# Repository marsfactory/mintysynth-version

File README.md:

# mintysynth-version
Rediseño de pcb del proyecto original de Andrew Mowry disponible en https://mintysynth.com/

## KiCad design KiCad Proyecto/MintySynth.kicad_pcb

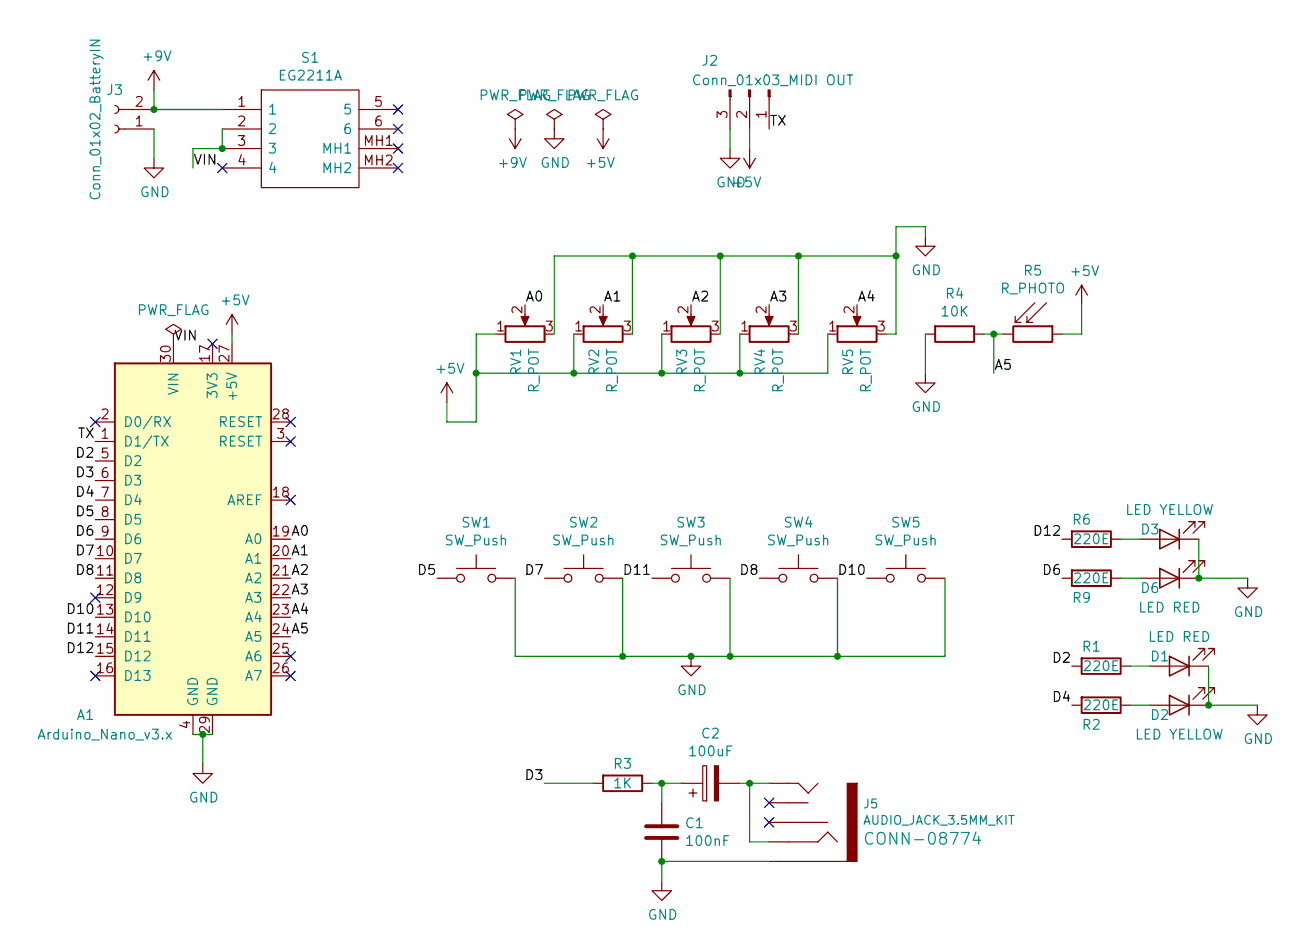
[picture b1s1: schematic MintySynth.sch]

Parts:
A1: Arduino_Nano_v3.x; Arduino_Nano
C1: 100nF; C_Disc_D3.8mm_W2.6mm_P2.50mm
C2: 100uF; CP_Radial_D5.0mm_P2.50mm
D1, D6: LED RED; LED_D5.0mm
D2, D3: LED YELLOW; LED_D5.0mm
J2: Conn_01x03_MIDI OUT; 1X03_LOCK
J3: Conn_01x02_BatteryIN; 1X02
J5: AUDIO_JACK_3.5MM_KIT; AUDIO-JACK-KIT
R1, R2, R6, R9: 220E; R_Axial_DIN0207_L6.3mm_D2.5mm_P10.16mm_Horizontal
R3: 1K; R_Axial_DIN0207_L6.3mm_D2.5mm_P10.16mm_Horizontal
R4: 10K; R_Axial_DIN0207_L6.3mm_D2.5mm_P10.16mm_Horizontal
R5: R_PHOTO; Resistor_LDR_5x4.1_RM3
RV1, RV2, RV3, RV4, RV5: R_POT; Potentiometer_Omeg_PC16PU_Horizontal_MountLS
S1: EG2211A; Mouser Part Number 612-EG2211A
SW1, SW2, SW3, SW4, SW5: SW_Push; SW_PUSH_6mm

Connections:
+5V: A1.27 (+5V), J2.2, R5.1, RV1.1, RV2.1, RV3.1, RV4.1, RV5.1
+9V: J3.2, S1.1
/A0: A1.19 (A0), RV1.2
/A1: A1.20 (A1), RV2.2
/A2: A1.21 (A2), RV3.2
/A3: A1.22 (A3), RV4.2
/A4: A1.23 (A4), RV5.2
/A5: A1.24 (A5), R4.1, R5.2
/D2: A1.5 (D2), R1.2
/D3: A1.6 (D3), R3.2
/D4: A1.7 (D4), R2.2
/D5: A1.8 (D5), SW1.1
/D6: A1.9 (D6), R9.2
/D7: A1.10 (D7), SW2.1
/D8: A1.11 (D8), SW4.1
/D10: A1.13 (D10), SW5.1
/D11: A1.14 (D11), SW3.1
/D12: A1.15 (D12), R6.2
/TX: A1.1 (D1/TX), J2.1
/VIN: A1.30 (VIN), S1.2, S1.3
GND: A1.4 (GND), A1.29 (GND), C1.2, D1.1 (K), D2.1 (K), D3.1 (K), D6.1 (K), J2.3, J3.1, J5.SLEE (SLEEVE), R4.2, RV1.3, RV2.3, RV3.3, RV4.3, RV5.3, SW1.2, SW2.2, SW3.2, SW4.2, SW5.2
unnamed: C1.1, C2.1, R3.1
unnamed: C2.2, J5.RING, J5.TIP
unnamed: D1.2 (A), R1.1
unnamed: D2.2 (A), R2.1
unnamed: D3.2 (A), R6.1
unnamed: D6.2 (A), R9.1

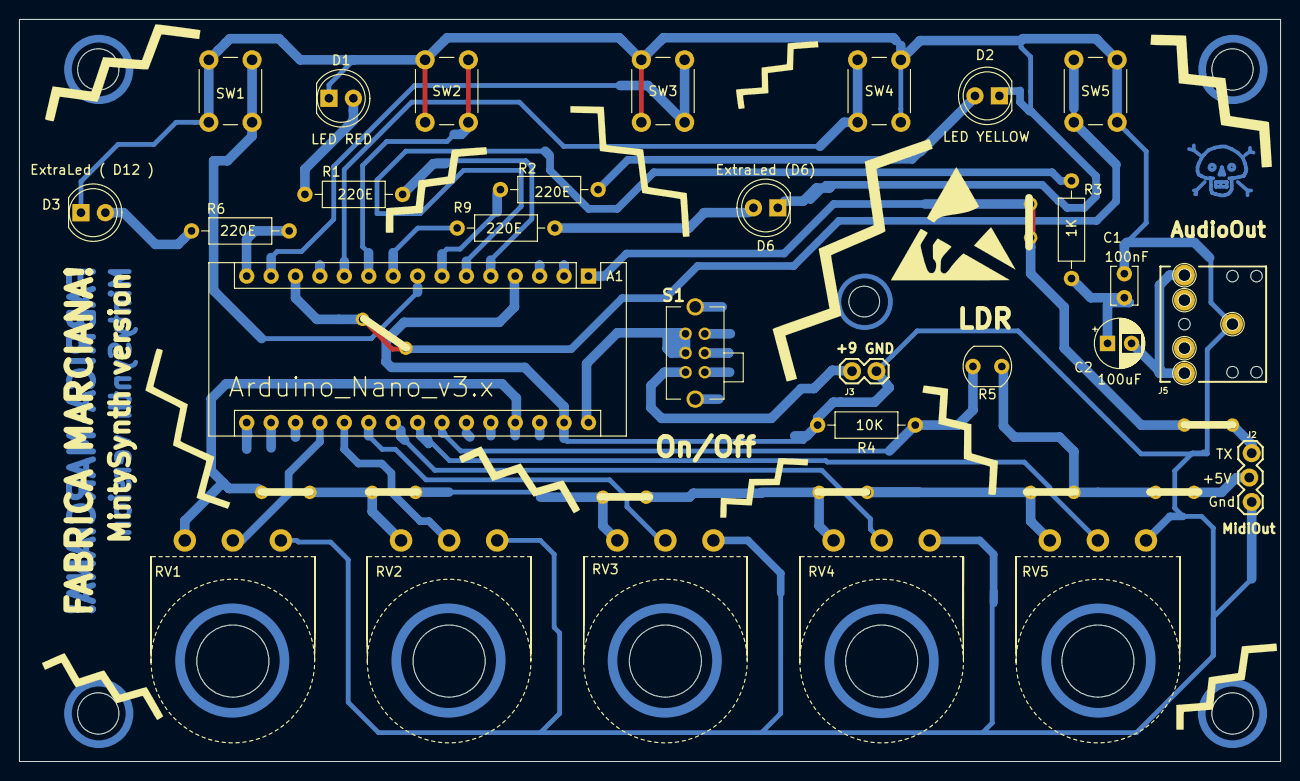
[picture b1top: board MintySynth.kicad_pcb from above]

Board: 2 copper layers, 131.2 x 77.2 mm, 29 parts (0 on the bottom side), 27 nets.

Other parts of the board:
e: MountingHole_4.3mm_M4_DIN965

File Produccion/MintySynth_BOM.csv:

Id;Identificador;Empaquetado;Cantidad;Identificación;Suministrador y ref
1;REF***;ESD-Logo_13.2x12mm_SilkScreen;1;ESD-Logo_13.2x12mm_SilkScreen;
2;REF**;MountingHole_3.2mm_M3;1;MountingHole_3.2mm_M3;
3;D3;LED_D5.0mm;1;ExtraLed (D12);
4;R6,R1,R2,R9;R_Axial_DIN0207_L6.3mm_D2.5mm_P10.16mm_Horizontal;4;220E;
5;D6;LED_D5.0mm;1;ExtraLed (D6);
6;REF**;Symbol_Danger_CopperTop_Small;1;Symbol_Danger_CopperTop_Small;
7;REF**,REF**,REF**,REF**,REF**,REF**,REF**,REF**,REF**;WireConnection_0.80mmDrill_ThinPad;9;WireConnection_0-8mmDrill_ThinPad;
8;REF**,REF**,REF**,e;MountingHole_4.3mm_M4_DIN965;4;MountingHole_4.3mm_M4_DIN965;
9;RV5,RV1,RV2,RV3,RV4;Potentiometer_Omeg_PC16PU_Horizontal_MountLS;5;R_POT;
10;A1;Arduino_Nano;1;Arduino_Nano_v3.x;
11;C1;C_Disc_D3.8mm_W2.6mm_P2.50mm;1;100nF;
12;C2;CP_Radial_D5.0mm_P2.50mm;1;100uF;
13;D1;LED_D5.0mm;1;RED;
14;D2;LED_D5.0mm;1;YELLOW;
15;J2;1X03_LOCK;1;Conn_01x03_MIDI OUT;
16;J3;1X02;1;Conn_01x02_BatteryIN;
17;J5;AUDIO-JACK-KIT;1;AUDIO_JACK_3.5MM_KIT;
18;R3;R_Axial_DIN0207_L6.3mm_D2.5mm_P10.16mm_Horizontal;1;1K;
19;R4;R_Axial_DIN0207_L6.3mm_D2.5mm_P10.16mm_Horizontal;1;10K;
20;R5;Resistor_LDR_5x4.1_RM3;1;R_PHOTO;
21;S1;EG2211A;1;EG2211A;
22;SW1,SW2,SW3,SW4,SW5;SW_PUSH_6mm;5;SW_Push;
